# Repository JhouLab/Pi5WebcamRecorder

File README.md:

# HOW TO USE:

Instructions, version 1.5, Updated March 10, 2025.

This is intended to run on a Raspberry Pi 5, which is much faster than the Pi 4. It
can handle 4 simultaneous cameras at 640x480 resolution and 30 frames per second.

It will run on an older Pi 4 (slowly), and is best suited for controlling a single camera.

If you have problems, questions, or suggestions, please email jhoulab1@gmail.com

# GETTING STARTED:

To install on a new machine, follow the instructions at the bottom of this page, under: "Installing on Raspberry Pi 5".

On most JhouLab Pi's, the program is already installed to the following folder:

    /home/jhoulab/Documents/github/Pi5WebcamRecorder

Once installed, launch the program with one of the following methods:

    Method 1: From command line:

      cd ~/Documents/github/Pi5WebcamRecorder
      python -m RUN_AS_ROOT

    Method 2: From the Pi's built-in Thonny app:
      Click "Load", select "RUN_AS_ROOT.py", then click "Run" (green button with white triangle).

Upon launch, the program will auto-detect USB cameras, open a control bar, and display up to 4 cameras in a 2x2 grid,
like below:

Cameras plugged into any of the four USB ports will show up on the screen in the following positions:

    -------------
    |  1  |  2  |
    -------------
    |  3  |  4  |
    -------------

The program will show a bar at the top with buttons to start/stop recording. You can also control recording
from external GPIO logic inputs (see "GPIO PROTOCOL" section below).

By default, videos save to the program directory, but I recommend you
change this to an external drive, to avoid filling up your SD card.
This is done by creating/editing a config.txt file (see CONFIGURING section below).

Default video format is 640x480, 30fps, with h264 encoding. These can also be
changed in config.txt.

Each recording session generates three files, with the following names and contents:

    YYYY-MM-DD_HHmm_CamX_AnimalID_Video.avi     # Video file in h264 format.
    YYYY-MM-DD_HHmm_CamX_AnimalID_Frames.txt    # Tab-delimited text file with timestamps of each video frame
    YYYY-MM-DD_HHmm_CamX_AnimalID_TTLs.txt      # Tab-delimited text file with timestamps of each TTL pulse

In the above filenames, YYYY-MM-DD_HHmm is the date and time, X is the camera number (1-4), and AnimalID is entered
manually or transmitted via GPIO logic inputs.

h264 codec is pretty efficient. Files are typically about 2MB/min, or 33kB/sec. This will reach 1GB after about 6-8 hours.

# CONFIGURING:

Many default parameters can be changed using a "config.txt" text file. I've included two working examples:

    config_example1     A detailed file with all possible configuration options
    config_example2     A bare-bones file with only the most commonly used options.

To use either file, open it in any text editor, resave it as "config.txt", then edit to suit your needs.
Changes to "config.txt" take effect only after restarting the program. Options include the following:

    RECORD_FRAME_RATE            # Frame rate of recorded video. If not specified, defaults to camera's native frame rate, typically 30fps
    NATIVE_FRAME_RATE            # Native frame rate of webcam. If not specified, will be auto-detected.
    DATA_FOLDER                  # Folder for saving. If not specified, defaults to program directory.
    RESOLUTION                   # A string of the form: (width,height), e.g. (640x480)
    FOURCC                       # Recording codec. Default h264 which gives smallest file sizes. Can also use mp4v, which is less CPU intensive, but gives larger files

# GPIO TIMING PROTOCOL

Pi5WebcamRecorder monitors GPIO inputs 4 through 7, corresponding to the following cameras:

    GPIO4:          camera 1
    GPIO5:          camera 2
    GPIO6:          camera 3
    GPIO7:          camera 4

These are 3.3V inputs, so you must use a level shifter when connecting to 5V devices. If you use Med-PC
to generate timing signals, remember that those are 28V signals, which require an additional
voltage shifter (purchased from Med Associates) to convert from 28V to 5V, which in turn is converted to 3.3V
through the level-shifter, i.e. you will need to devices. Setting these up requires some
familiarity with electronics.

Sending two consecutive 100ms pulses (with a 50ms pause in between) will start a recording, as follows:

            100ms  100ms
    3.3V     ___    ___      
            |   |  |   |    
    0V -----     --     --------
                50ms

Once a session is started, three consecutive 100ms pulses will stop the recording:

            100ms  100ms  100ms
    3.3V     ___    ___    ___    
            |   |  |   |  |   |
    0V -----     --     --     ----
                50ms    50ms

While a recording is ongoing, any single 100ms pulse will be recorded in the *_TTLs.txt file.
The pulse will look like this:

            100ms
    3.3V     ___ 
            |   |
    0V -----     ----------

The contents of the *_TTLs.txt file will be tab-delimited, and will will have three columns,
corresponding to event number, onset time, and offset time:

    TTL_event_number	ONSET (seconds)	OFFSET (seconds)
    1	19.604753732681274	19.708051204681396
    2	155.62897396087646	155.73339176177979
    3	411.64712834358215	411.75243949890137
    4	607.6641576290131	607.7683758735657
    5	803.6808965206146	803.7854342460632
    6	1059.6991975307465	1059.8032557964325

With all pulses, the allowable range is 50-150ms, but it is recommended not to get too close to
the endpoints of this range, as errors can occur due to Linux not being a real-time operating system.

You can also transmit an animal ID number via the GPIO pins as a 16-bit binary number.
The ID number has to be transmitted BEFORE starting the session, and will show up
in the filename and on the screen during recording.

If you transmit the ID after a session has already started, it will likely
get interpreted as a triple pulse, which will stop the recording. So don't do that.

ID transmission begins with a 300ms pulse, followed by 16 binary bits as shown below:

    3.3V      300ms  <16 binary bits, 50 or 150ms each>            <Parity bit 50 or 150ms long>
             ______   _   _   ___   _   ___                 _       _
            |      | | | | | |   | | | |   |  .. etc..     | |     | |
    0V -----        -   -   -     -   -     -             -   -----   ---------------
                      50ms between ID bits                    200ms pause before parity bit

The bit order is MOST significant bit first, 50ms pulse for "0" and 150ms pulse for "1", and 50ms gaps between pulses.
The final checksum parity bit is 50ms duration if the preceding ID had an even number of "1"s, 150ms duration if odd.

# KNOWN SHORTCOMINGS:

1. The last frame of video may not be recorded to the hard drive. This appears to be a bug in FFMPEG, which OpenCV uses.

2. On Windows, it is convenient to use ImageJ/FIJI to quickly view videos, but this does not appear
   to work on the Raspberry Pi, again due to issues with FFMPEG. A cumbersome workaround is to decompress video using:
     
         ffmpeg input.avi -c:v rawvideo output.avi

#  INSTALLING ON RASPBERRY PI 5:

To install, follow these three steps:

### STEP 1: Clone the github repository.

  There are two ways to do this:

  #### Method 1: From command prompt:
    
    git clone https://github.com/JhouLab/Pi5WebcamRecorder

  #### Method 2: Using Github Desktop: https://pi-apps.io/install-app/install-github-desktop-on-raspberry-pi/

  First install Pi-Apps:

    wget -qO- https://raw.githubusercontent.com/Botspot/pi-apps/master/install | bash

  Launch Pi-Apps, select "Programming", "Github Desktop" (the purple cat icon), and
  click "Install". It will take a couple of minutes. Then launch Github from the main Raspberry Pi menu,
  under "Accessories", then log into the lab github account. Then select "File",
  "Clone repository", "Github.com", "JhouLab/Pi5WebcamRecorder":

  Github Desktop only works on Pis running a 64-bit os. If you are running a 32-bit
  os, it may still install, but graphics will be weird and unusable.

## STEP 2: Install OpenCV.

  From the command prompt, type the following:

    sudo apt-get install libopencv-dev
    sudo apt-get install python3-opencv

  As of 6/12/2024, this installs OpenCV version 4.6.0, which is outdated (released 6/12/2022),
  but works well enough. For other ways to install OpenCV, see here:
  https://qengineering.eu/install%20opencv%20on%20raspberry%20pi%205.html

## STEP 3: Install rpi-lpgio (needed for older Pi's, prior to bookworm OS, if controlling from external GPIOs)
  The Pi5 uses different GPIO hardware than the Pi4, but the default GPIO library up to 2023 assumed
  the old hardware, requiring one to manually replace it with python3-rpi-lpgio. Starting in late 2023 with
  Bookworm OS, this is no longer required as it is included by default:

    sudo apt remove  python3-rpi.gpio
    sudo apt install python3-rpi-lgpio

## STEP 4: If saving to network storage, need to add SMB client and tailscale

From the command line, install both:

    sudo apt upgrade
    sudo apt install cifs-utils smbclient -y
    curl -fsSL https://tailscale.com/install.sh | sh
    sudo tailscale up

When you run this, it should open a browser window into which you should log
into the lab tailscale account. If not, you will see a link that you can
right click to manually open. Then sign into your tailscale account.
It might take a couple of tries for this to work. When done, the console
window should report "Success." and return you to the Linux prompt. If
you don't see that, it didn't work yet.

After this, it will automatically reconnect when rebooting Pi, and you don't need to restart it again.

Optional: can use this to prevent tailscale up from requiring sudo

	sudo tailscale set --operator=$USER

Now install smb client:

	sudo apt-get install  samba-common smbclient samba-common-bin smbclient  cifs-utils
    
Make folder and mount shared folder there. The mount does not persist after Pi restart:

	sudo mkdir /mnt/share_name_here
	sudo mount -t cifs //labunraid/zfs48_share /mnt/share_name_here -o user=tomjhou,pass=ithaca55,uid=1000,gid=1000

To ensure this works every time, add the following line to config.txt:

    LINUX_START_SCRIPT = sudo mkdir -p /mnt/share_name_here && sudo mount -t cifs //labunraid/zfs48_share /mnt/share_name_here -o user=tomjhou,pass=ithaca55,uid=1000,gid=1000

Note the mkdir "-p" option to suppress error if folder already exists. Somehow on raspberry pi, mount will still run even if mkdir throws error. Not sure why,
as "&&" shouldn't allow that. Not actually a problem, just curious behavior. If mount exists, will throw "device or resource busy error". This can be safely ignored.

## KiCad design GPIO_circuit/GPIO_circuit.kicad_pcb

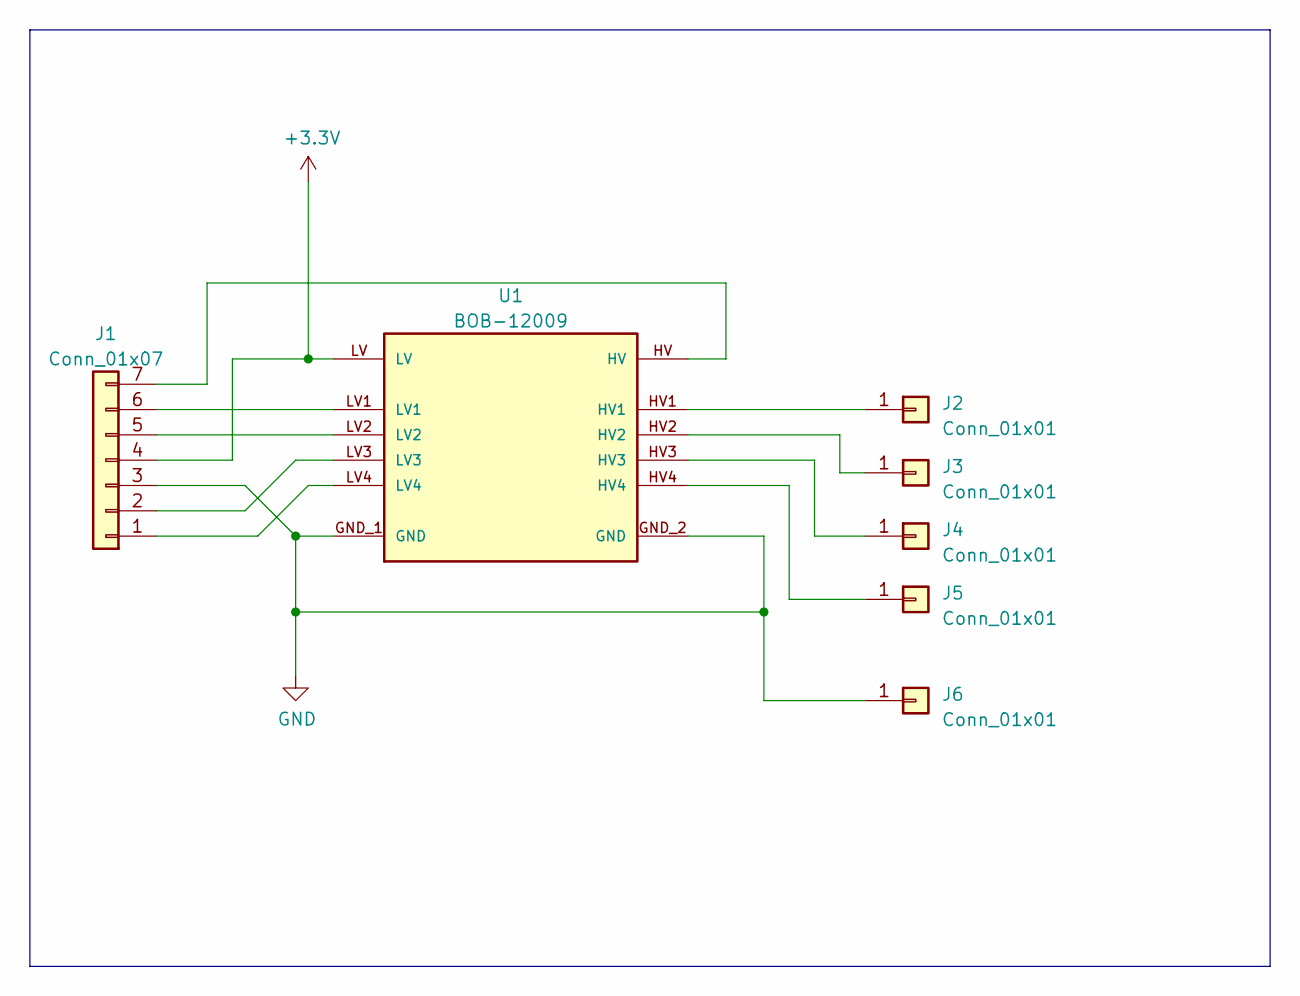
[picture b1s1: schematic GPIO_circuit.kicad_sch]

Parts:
J1: Conn_01x07; PinHeader_1x07_P2.54mm_Horizontal
J2, J3, J4, J5: Conn_01x01; Pad_for_BNC
J6: Conn_01x01; PinHeader_1x01_P1.00mm_Vertical
U1: BOB-12009; CONV_BOB-12009; PARTREV 01

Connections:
+3V3: J1.4, U1.LV
GND: J1.3, J6.1, U1.GND_1 (GND), U1.GND_2 (GND)
unnamed: J1.1, U1.LV4
unnamed: J1.2, U1.LV3
unnamed: J1.5, U1.LV2
unnamed: J1.6, U1.LV1
unnamed: J1.7, U1.HV
unnamed: J2.1, U1.HV1
unnamed: J3.1, U1.HV2
unnamed: J4.1, U1.HV3
unnamed: J5.1, U1.HV4

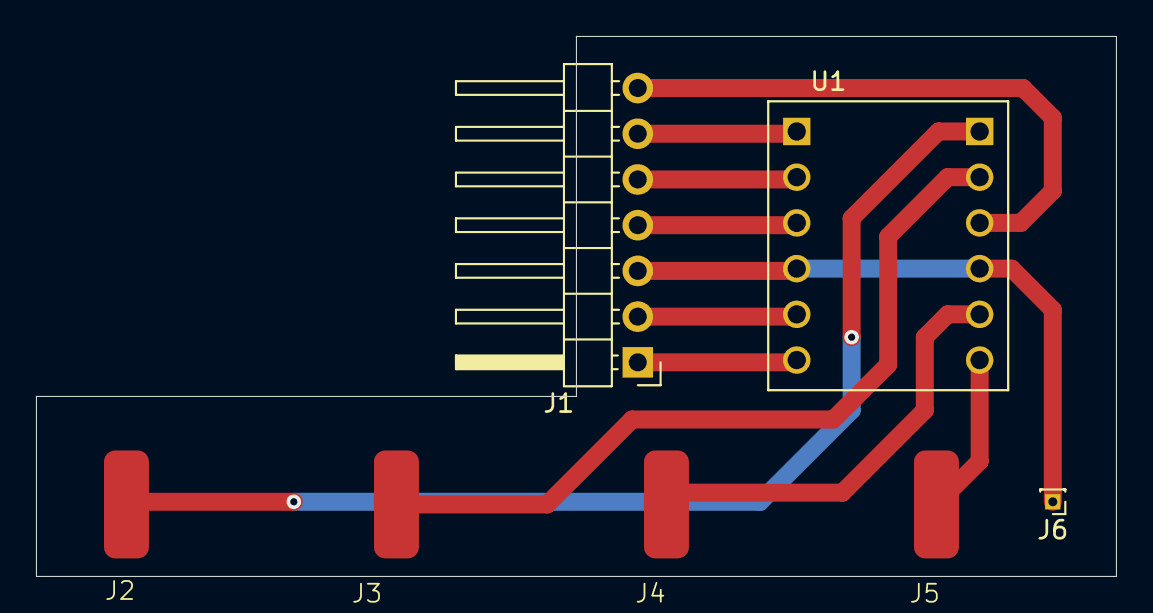
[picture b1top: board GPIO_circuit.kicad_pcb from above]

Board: 2 copper layers, 60.0 x 30.0 mm, 7 parts (0 on the bottom side), 11 nets.

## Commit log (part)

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2024-06-06 Updates to speed up on Windows. Add .gitignore
2024-06-07 Added USB port detection and independent recording ability, triggered by keyboard
    Camera number (and screen position) now corresponds to USB port location on Pi5. Typing keyboard values 0-3 starts/stops recording in that camera.
2024-06-07 Modifications so that keypress detection works on Windows
    Also suppresses USB port detection on Windows, since the detection code is Linux-only (and probably Pi-only)
2024-06-09 Added GPIO code (not yet tested)
2024-06-10 Very minor bug fix, and increased precision of camera elapsed time report.
2024-06-10 Rename INSTRUCTIONS_README to README
2024-06-10 Added error handler in case GPIO setup fails
    Will now warn user if you are running on a Pi5 and have not yet replaced the gpio library.
2024-06-12 Session now starts AND stops with double-pulse TTLs only. NOT YET TESTED.
    Med-PC double-pulses are 1 second apart. We accept anything <2.0 sec apart just in case there are minor delays.
2024-06-12 IMPORTANT BUG FIX FOR MANUAL RECORDING
    Fixed bug that prevents manual recording from starting.
2024-06-12 VERSION 1.0, with updated instructions.
2024-06-13 VERSION 1.1, added option for configuration file to specify folder path, codec, FPS, etc.
2024-06-13 Fixed bug when closing all 4 files at once.
    Also updated debugging "d" function to apply to all cameras, not just one.
2024-06-14 VERSION 1.2, updated instructions, better support for resolutions besides 640x480
    Screen fonts are now scaled to match frame resolution.
2024-06-15 Added code to print timestamp to screen for significant events
2024-06-16 Added flush so that log file is written immediately.
    Otherwise, log events sometimes can't be read until much later, or after program exits.
2024-06-18 Changed from pullup to pulldown resistor, to reduce glitching on TTLs
2024-06-19 Now shows blue dot on frames where GPIO is detected.
2024-06-22 NOT TESTED: Added new code to handle binary mode transmission of animal ID
2024-06-24 Fixed GPIO bug
    Also fixed issue where blank folder would get an unnecessary slash added to the end.
2024-06-29 Store binary animal ID in temporary variable until fully calculated
    Unwind some of the CPU lag modifications made before.
2024-06-30 Checksum code WORKS now.
2024-06-30 Now uses GPIO low period duration to distinguish bursts.
    This improves burst rejection
2024-07-01 Fixed bug that caused crash if only one cam present and not in first USB position
2024-07-01 Minor simplification to key detect code
2024-07-05 Updated README. Increased timing leeway for stopping binary mode.
2024-07-08 Version1.4 Now integrated with tkinter. STILL BUGGY.
2024-07-09 Fixed Linux-specific bugs.
2024-07-09 Added keycodes for Raspberry pi arrow keys
2024-07-09 Added window title
2024-07-09 Fixed bug causing crash if camera status is false
2024-07-09 Add elapsed time reporting to GUI
2024-07-09 Fixed bug in CPU lag calculation
2024-07-10 Tkinter window is now separate from cv2 window. This allows much faster video rendering.
2024-07-10 Added button to stop all ongoing recordings
2024-07-10 Handle key press in either tkinter or cv2 window
2024-07-10 Added pygame test. This is a (likely to be abandoned) attempt to speed up video rendering in tkinter window.
2024-07-10 Attempt to fix glitch on Pi when exiting.
    Apparently there is a call to update_image in the queue when root is destroyed (which terminates the program and destroys the entire Recording class)
2024-07-10 Added second row of control buttons to cycle through cameras
2024-07-10 Added check for back-compatibility with older slower Med-PC TTL pulses
2024-07-10 Bug fix for moveWindow on Pi
2024-07-10 Added lock to CamObj.read() to prevent glitches when starting/stopping recording.
    Some status print statements now occur in VERBOSE mode only, as they weren't necessary in everyday use.
2024-07-10 Fixed bugs related to start/stop button enabling. Updated instructions.
2024-07-11 Fixed bug causing deadlock when session is started/stopped remotely.
    Also improved type hints in CamObj.py
2024-07-11 recording status reports fps now
2024-07-12 Stress test now writes files.
2024-07-18 Fixed bug causing DATA_FOLDER to be concatenated twice. Simplified creation of save-to directory.
2024-07-22 Added code to more easily exit DEBUG TTL mode if it is accidentally triggered.
2024-07-23 Clarification to comments about libraries PIL, tkinter, cv2, and numpy
2024-07-23 Moved test code to "extra" folder to reduce clutter in top level
2024-07-24 Additional debug time diagnostics added.
2024-07-24 Greatly improved timing diagnostics in DEBUG mode
2024-07-24 Added option for snapshot button.
2024-07-25 Adjusted display drop algorithm to avoid dropping frames at very high lags (which usually mean that frame rate is set too high)
    Also added zoom button option to example config file
2024-07-30 Now issues warning if data folder is missing.
2024-08-01 Blue dot now stays on for entire duration that GPIO is high. Animal ID text moved down slightly to avoid overlapping blue dot.
2024-08-01 Added diagnostics if camera connection fails.
2024-08-02 Improved frame rate profiling and resolution configuration
    Profiling now takes constant time regardless of frame rate, and resolution can now be specified as a tuple.
2024-08-02 Now writes frame number to video. Removed helper thread for stopping recording, as it is no longer needed.
2024-08-02 Improvement to profiling on Pi
2024-08-02 Improved queue-based frame handling
    This will allow CPU usage monitoring, and also confers some robustness to minor CPU delays as frames can be buffered in the queue.
2024-08-02 Fixed three bugs:
    Bug causing crash if no native fps is given in config.txt, bug preventing "disconnect" message from showing if only one camera is displayed, and bug preventing a second recording session from startin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
2024-08-03 Slight simplification to process_frame()
2024-08-03 Updated documentation. root.withdraw() now done on all platforms.
2024-08-04 Pi display rate reduced to 10fps. Adjusted on-screen info to avoid overlap.
2024-08-04 Added comment about GPIO.setup()
2024-08-04 Added new file to test missing last frame problem
2024-08-05 Now saves TTL offset time, so that TTL duration can be determined
2024-08-05 Fixed bug where root window didn't get destroyed at end. Delayed launch of GUI until after profiling is done. Removed buttons from cv2 window (since they look weird in superuser mode). Added RUN_THIS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
2024-08-05 Process priority stuff now auto-detects Linux vs Windows
2024-08-06 Multiprocessing code
2024-08-06 Bug fixes affecting Pi and GPIO handling.
2024-08-06 Added slight delay so that profiling results come back in numerical order by camera.
2024-08-06 Fixed window resize issue when running as root. Improved lag detection.
2024-08-06 Renamed file
2024-08-07 Using memory-mapped queue
2024-08-07 Camera disconnect message works again.
    More code streamlining.
2024-08-07 Added flush to printt, or else text doesn't show right away when running as root.
2024-08-07 Renamed variable for clarity
2024-08-07 Streamlining and renamed variables for clarity. Moved get_hardware_info.py to extra folder
2024-08-07 More GPIO testing...
2024-08-07 Moved GPIO back to parent process
2024-08-07 Now avoids simultaneous camera CPU lag warnings.
2024-08-07 Add CPU lag report
2024-08-07 CPU lag improvements
2024-08-07 Debug mode now writes CPU lag to frames.txt
2024-08-07 fixed polling option bug
2024-08-07 More debug diagnostic info in txt files.
2024-08-08 Using GPIO callback is now a config setting.
2024-08-08 Fixed checksum bug to handle new longer binary bits.
2024-08-08 GPIO callback now defaults to False
2024-08-08 Compression lag warnings now only appear in DEBUG mode, since they are generally harmless.
2024-08-08 Reduce processing of any cameras not being shown in GUI
2024-08-08 Fixed bugs relating to snapshot mode
2024-08-08 Snapshot now prompts for filename
2024-08-09 Renamed SHOW_ON_SCREEN_INFO to SAVE_ON_SCREEN_INFO
2024-08-09 Fixed bug causing file manager to open as root. Fixed bug causing XDG_RUNTIME_DIR error
2024-08-11 Updates so that File Manager works correctly when opened while running as root
    Basically we copy XDG_RUNTIME_DIR into a temporary variable so we can restore it when we "downgrade" from root back to a normal user. Weird that we have to do this, but I haven't found a cleaner way 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
2024-08-12 Updated comments
2024-08-12 Fixed bug affecting user account detection if SUDO_USER fails. Added code to explicitly wait for all CamObj threads to exit.
2024-08-12 Fixed bug causing crash in boxes where no camera exists.
2024-08-12 Added defaults for CamObj when camera not detected.
2024-08-13 Removed unnecessary GPIO setup, now that we fixed the bug where GPIO 0 was being erroneously set up multiple times.
2024-08-26 Now attempts to reconnect if camera is unplugged.
2024-08-27 Port change warning works correctly now.
2024-08-27 Switch from jpg to png (lossless) snapshots.
2024-08-28 Adds PNG ending if not already present
2024-08-28 TTL file now flushes regularly, to reduce data loss during crash. Diagnostic to file if CPU lag is high.
    Added type hint for file stream variables.
2024-08-30 Diagnostic now includes frame #, frame time, and processing lag
2024-08-30 Minor clarifications to comments and formatting.
2024-09-01 Stress-test now flickers to truly stress out compression algorithm
2024-09-01 More improvements to diagnostic logging
2024-09-01 Now showing dropped frames in status line.
2024-09-01 Minor updates to comments
2024-09-02 Now avoids writing TTLs that arrive after stop command is issued (but that may occur while still processing queued video frames)
2024-09-02 All directories are now created with 777 permissions
2024-09-03 Now drops frames pre-emptively to avoid overloading queue
2024-09-03 Added diagnostic if text file write generates error.
2024-09-20 Fixed Pi model detector (now tested)
2024-09-23 Minor cleanup
2024-09-26 Added screenshot to README.md
2024-09-27 Update .gitignore to ignore log files
2024-09-27 Updated comments. Updated .gitignore to ignore Frames.txt, TTLs.txt, and diagnostic.txt.
2024-09-30 Added PCB board files
2024-11-04 Camera ID display now works even if zoomed in.
2024-11-05 Camera resolution warning now goes to dialog box as well as console.
2025-03-13 Fixed errors in GitHub instructions, and corrected/clarified CamObj.py comments.
2025-10-10 Added rotate180 config option, added check for invalid config entries. Improved warning instrucitons.
2025-10-17 Now stops recording when <20MB disk space left.
2025-10-18 Improved error reporting if config.txt is not present or has invalid entries
2026-01-07 Added ability to specify multiple data folders, separated by semicolon
2026-01-07 Added ability to run linux command on startup, useful for mounting SMB shared folder.
2026-03-26 Fixed bug involving race condition in mkdir(). README clarifications for SMB sharing.
2026-03-31 Improved handling of network drives - first saves to local folder, then copies to network drive.
2026-03-31 More cleanup and refactoring. Fixed bugs in which log text file was missing newlines.
2026-03-31 Network drive stuff is wrapped into CopyManager object for streamlining.
2026-03-31 File copy thread now only copies avi and txt files.
2026-04-01 Added config for Mouse3
2026-04-01 Moved disk storage report to left side, where it has more space
2026-04-01 Fixed bug in disk space reporting introduced by last update
2026-04-01 Updates so that code will not try to make unique filenames for stress_test recordings. Also fixed debug detection for pycharm
